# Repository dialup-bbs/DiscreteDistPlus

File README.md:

This is a clone of a classic distortion guitar pedal circuit that has been designed to be used with K7TFC's all discrete LM741 op-amp.

This circuit has not been tested, so I do not suggest trying to build it without looking at it first. 3 prototype boards are currently being fabricated. 

This is also my first KiCad project and as a builder, I am completely unexperienced as a circuit drafter/designer. 

A huge thanks to K7TFC/Mostly DIY RF for their incredibly inspirational work on the OA741D.

Please visit:

https://github.com/mostlydiyrf/OA741D

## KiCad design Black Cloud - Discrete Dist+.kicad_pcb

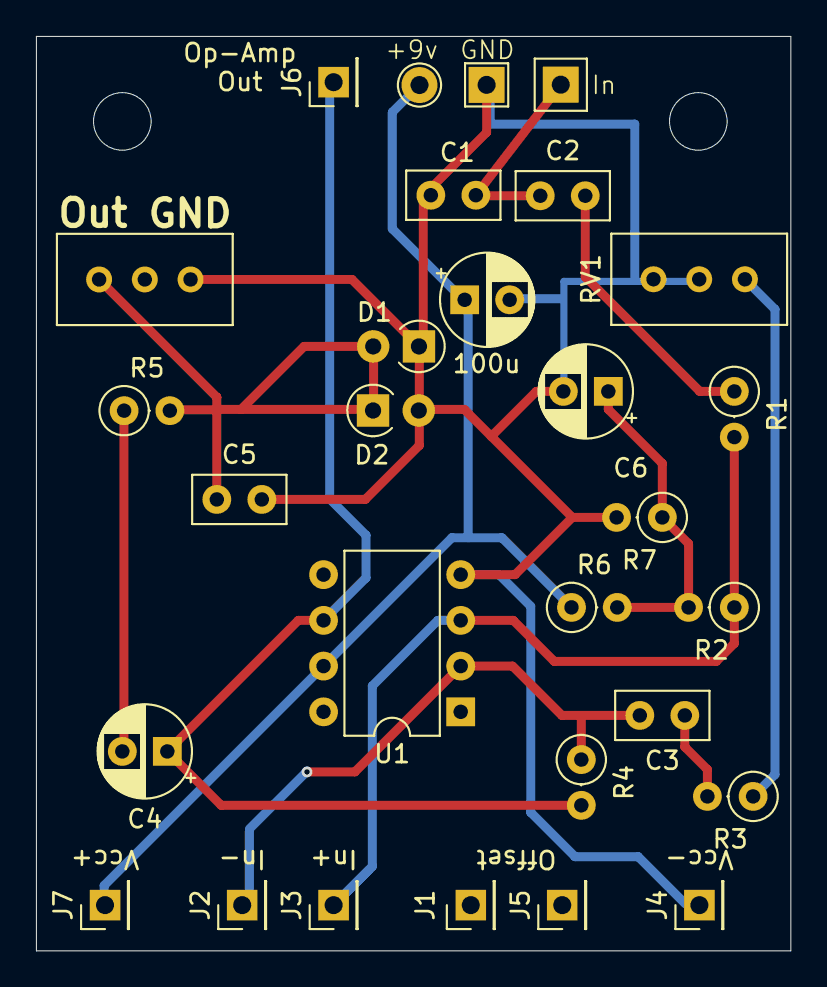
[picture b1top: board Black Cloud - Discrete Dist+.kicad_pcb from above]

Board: 2 copper layers, 41.9 x 50.8 mm, 29 parts (0 on the bottom side), 10 nets.

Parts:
100u: CP_Radial_D5.0mm_P2.50mm
+9v: TestPoint_THTPad_D2.0mm_Drill1.0mm
C1: 1nF; C_Disc_D5.0mm_W2.5mm_P2.50mm
C2: 10nF; C_Disc_D5.0mm_W2.5mm_P2.50mm
C3: 47nF; C_Disc_D5.0mm_W2.5mm_P2.50mm
C4: 1uF; CP_Radial_D5.0mm_P2.50mm
C5: 1n; C_Disc_D5.0mm_W2.5mm_P2.50mm
C6: 1u; CP_Radial_D5.0mm_P2.50mm
D1, D2: D_A-405_P2.54mm_Vertical_AnodeUp
GND: TestPoint_THTPad_2.0x2.0mm_Drill1.0mm
IN: TestPoint_THTPad_2.5x2.5mm_Drill1.2mm
J1, J2, J3, J4, J5, J6, J7: Conn_01x01; PinHeader_1x01_P2.54mm_Vertical
Out1: 10k; Potentiometer_Bourns_3386C_Horizontal
R1, R5: 10k; R_Axial_DIN0207_L6.3mm_D2.5mm_P2.54mm_Vertical
R2, R4, R6, R7: 1M; R_Axial_DIN0207_L6.3mm_D2.5mm_P2.54mm_Vertical
R3: 4.7k; R_Axial_DIN0207_L6.3mm_D2.5mm_P2.54mm_Vertical
RV1: 1M; Potentiometer_Bourns_3386C_Horizontal
U1: LM741; DIP-8_W7.62mm

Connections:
+4.5V: C6.1, R2.2, R6.2, R7.1
+9V: +9v.1, C5.1, D1.2 (A), D2.1 (K), J7.1, Out1.3, R5.2, R6.1, U1.7 (V+)
GND: C1.2, C5.2, C6.2, D1.1 (K), D2.2 (A), GND.1, J4.1, Out1.1, R7.2, RV1.1, RV1.2, U1.4 (V-)
unnamed: C2.2, R1.1
unnamed: C3.1, R3.2
unnamed: C4.1, J6.1, R4.2, U1.6
unnamed: C4.2, R5.1
unnamed: R3.1, RV1.3
unnamed: J3.1, R1.2, R2.1, U1.3 (+)
unnamed: C3.2, J2.1, R4.1, U1.2 (-)
